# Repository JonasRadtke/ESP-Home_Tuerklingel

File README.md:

# ESP-Home Tuerklingel

Dies Projekt bringt meine alte Türklingel bzw den Türöffner in Home-Assistent über ESP-Home.

- ESP8266 - muss vorher geflasht werden, bevor es auf das Board gelötet wird. Danach kann OTA geupdatet werden.
- 2x Optokoppler - für Klingelknopf unten und Klingelknopf oben
- 1x Mosfet-Relais - zum bedienen des Türöffners

Meine Türklingel wird per 8V Trafo aus dem Keller versorgt. Auch die Signale sind demnach 8V.

ESP-Home Home-Assistant Config in der YAML Datei.

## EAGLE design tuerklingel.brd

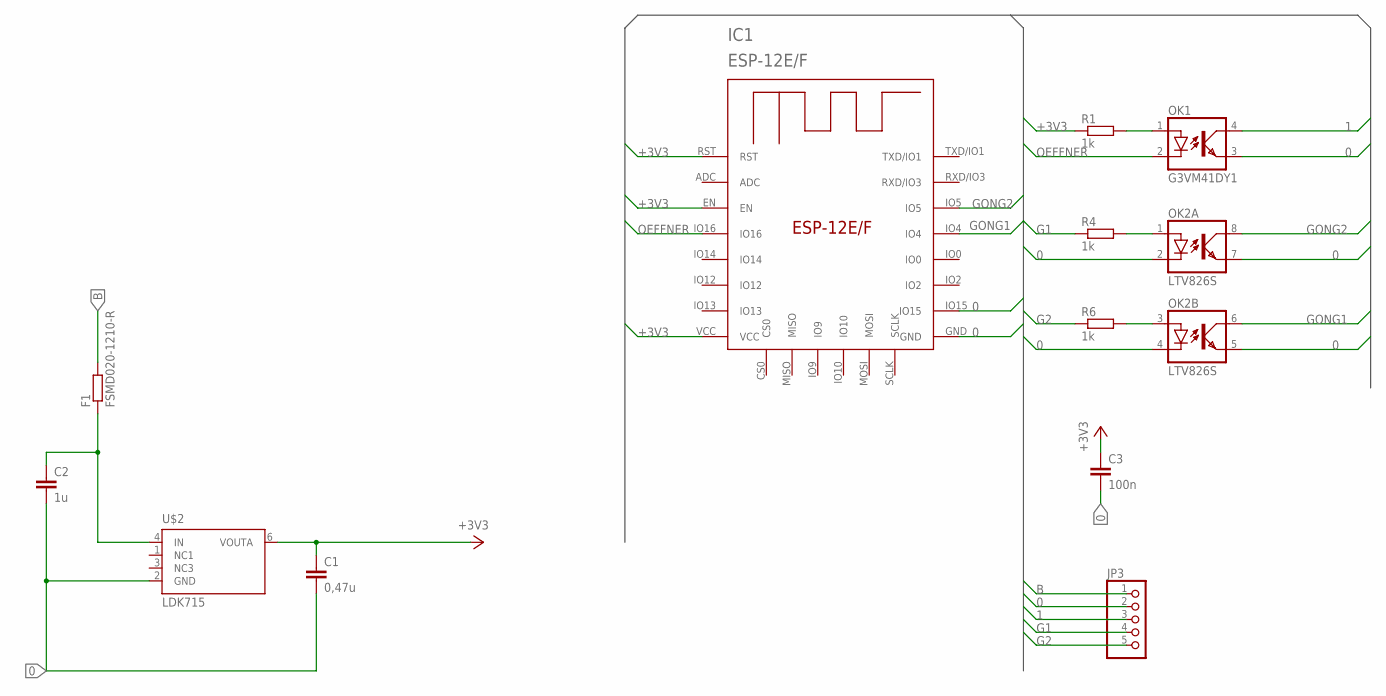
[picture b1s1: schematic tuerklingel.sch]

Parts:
C1: 0,47u; C0805
C2: 1u; C0805
C3: 100n; C0805
F1: FSMD020-1210-R; R1210
IC1: ESP-12E/F; ESP-12E
JP3: PINHD-1X5; 1X05
OK1: G3VM41DY1; DIL4-SMD
OK2: LTV826S; DIL8-SMD
R1, R4, R6: 1k; R0805
U$2: LDK715; SOT23-6

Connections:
0: C1.2, C2.2, C3.2, IC1.GND, IC1.IO15, JP3.2, OK1.3 (EMIT), OK2.2 (C), OK2.4 (C), OK2.5 (EMIT), OK2.7 (EMIT), U$2.2 (GND)
1: JP3.3, OK1.4 (COL)
+3V3: C1.1, C3.1, IC1.EN, IC1.RST, IC1.VCC, R1.1, U$2.6 (VOUTA)
B: F1.2, JP3.1
G1: JP3.4, R4.1
G2: JP3.5, R6.1
GONG1: IC1.IO4, OK2.6 (COL)
GONG2: IC1.IO5, OK2.8 (COL)
unnamed: C2.1, F1.1, U$2.4 (IN)
unnamed: OK1.1 (A), R1.2
unnamed: OK2.1 (A), R4.2
unnamed: OK2.3 (A), R6.2
OEFFNER: IC1.IO16, OK1.2 (C)

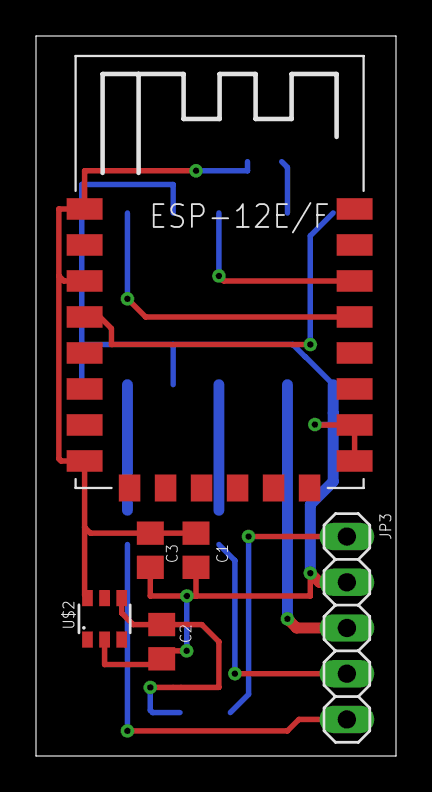
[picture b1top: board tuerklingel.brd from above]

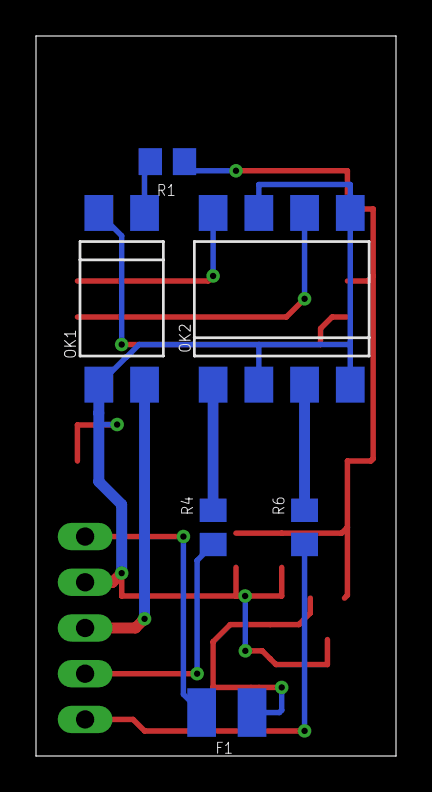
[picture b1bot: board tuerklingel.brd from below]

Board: 2 copper layers, 20.0 x 40.0 mm, 12 parts (6 on the bottom side), 13 nets.

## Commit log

2025-01-03 board+yaml
2025-01-03 bauteilbezeichnungen
2025-01-03 readme
